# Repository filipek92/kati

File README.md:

# kati - card access system

Kati is access system developed for [club Buben](http://www.buk.cvut.cz) of [CTU Student Union](http://su.cvut.cz).

Authentication and authorization is performed by these steps:

1. user attaches identification card to reader located near the door
2. reader parses identification of the card
3. authorization request is send to IS to perform authorization and authentication
3. access to the door is granted or denied according to reply from IS server

[RaspberryPi](https://www.raspberrypi.org/) is used as remote controller located near the door.

## Deployment

Assuming you have working SSH key-based login to hosts:

```sh
cd deploy
vim hosts # edit according to your needs
ansible-playbook deploy.yml
```

## Testing

SSH to a testing Raspberry and run:

```sh
cd ~/kati
python3 start.py
```

You can also try only specific components:

```sh
python3 -m kati.reader
python3 -m kati.lock
```

Or run tests (which are heavily WIP):

```sh
python3 -m nose
```

## Developers

- [Pavel Trutman](https://github.com/PavelTrutman)
- [Tomáš Bedřich](https://github.com/tomasbedrich)
- [Tomáš Kukrál](https://github.com/tomkukral)

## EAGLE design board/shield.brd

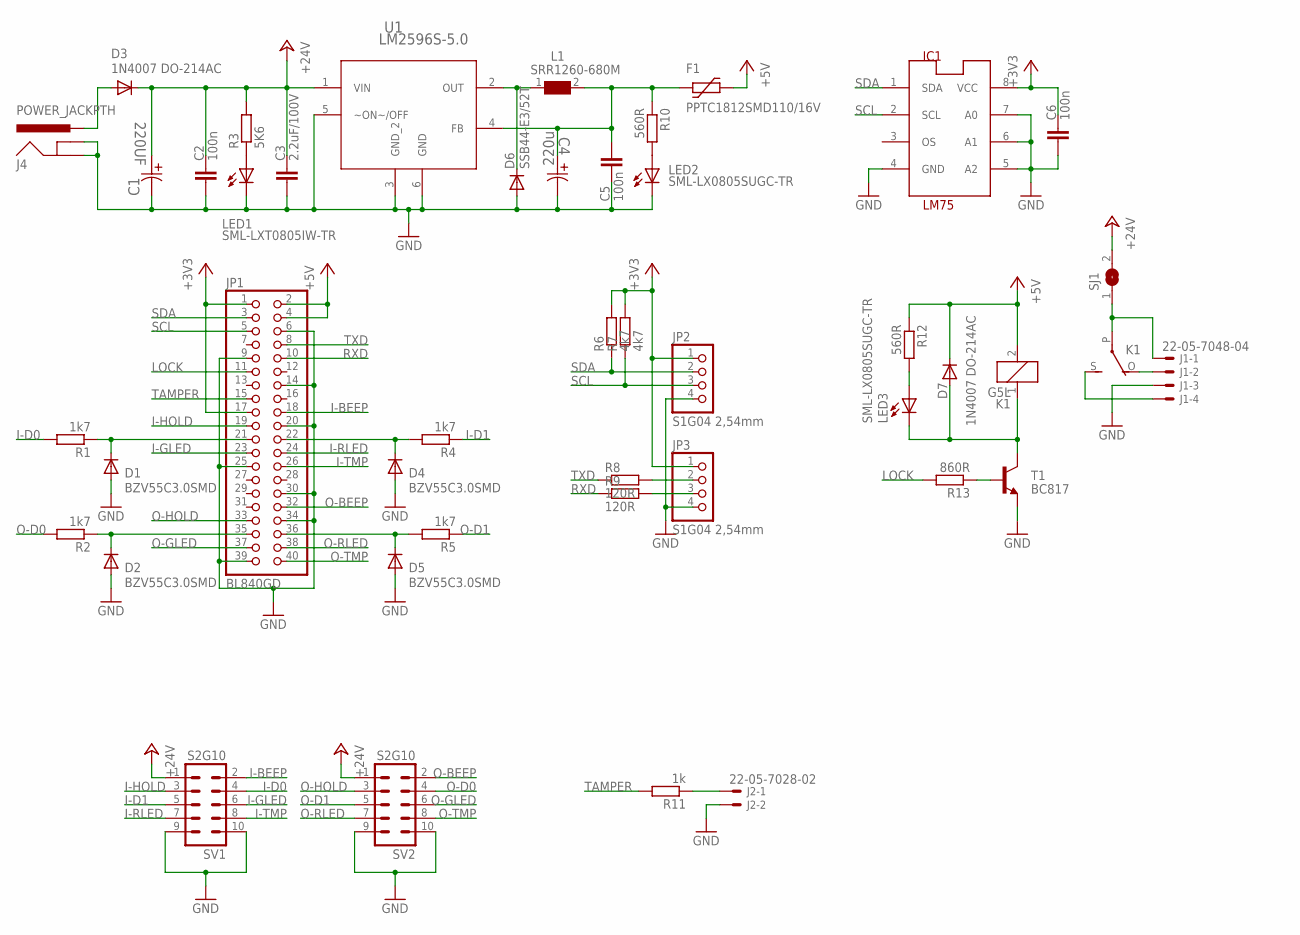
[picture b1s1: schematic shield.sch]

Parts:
C1: 220UF; CAPAE830X1050N
C2, C5, C6: 100n; C0805
C3: 2.2uF/100V; C1206
C4: 220u; CAPAE830X1050N
D1, D2, D4, D5: BZV55C3.0SMD; MINIMELF
D3, D7: 1N4007 DO-214AC; DO-214AC
D6: SSB44-E3/52T; DO214AA
F1: PPTC1812SMD110/16V; 1812L
IC1: LM75; SO8_LM75
J1: 22-05-7048-04; 7395-04
J2: 22-05-7028-02; 7395-02
J4: POWER_JACKPTH; POWER_JACK_PTH
JP1: BL840GD; 2X20
JP2, JP3: S1G04 2,54mm; 1X04
K1: G5L; G5LE
L1: SRR1260-680M; WE-PD_1260/1245/1280/1210
LED1: SML-LXT0805IW-TR; CHIPLED_0805
LED2, LED3: SML-LX0805SUGC-TR; CHIPLED_0805
R1, R2, R4, R5: 1k7; R0805
R3: 5K6; R0805
R6, R7: 4k7; R0805
R8, R9: 120R; R0805
R10, R12: 560R; R0805
R11: 1k; R0805
R13: 860R; R0805
SJ1: SJ
SV1, SV2: S2G10; MA05-2
T1: BC817; SOT23-BEC
U1: LM2596S-5.0; TO170P1435X465-6N

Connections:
+3V3: C6.2, IC1.8 (VCC), JP1.1, JP1.17, JP2.1, JP3.1, R6.2, R7.2
+5V: D7.C, F1.P$2 (2), JP1.2, JP1.4, K1.2, R12.1
+24V: C1.1, C2.2, C3.1, D3.C, R3.2, SJ1.2, SV1.1, SV2.1, U1.1 (VIN)
C: J1.1, K1.P, SJ1.1
GND: C1.2, C2.1, C3.2, C4.2, C5.1, C6.1, D1.A, D2.A, D4.A, D5.A, D6.A, IC1.4 (GND), IC1.5 (A2), IC1.6 (A1), IC1.7 (A0), J1.3, J2.2, J4.GND, J4.GNDBREAK, JP1.6, JP1.9, JP1.14, JP1.20, JP1.25, JP1.30, JP1.34, JP1.39, JP2.4, JP3.4, LED1.C, LED2.C, SV1.9, SV1.10, SV2.9, SV2.10, T1.E, U1.3 (GND_2), U1.5 (~ON~/OFF), U1.6 (GND)
I-BEEP: JP1.18, SV1.2
I-D0: R1.2, SV1.4
I-D0-3V3: D1.C, JP1.21, R1.1
I-D1: R4.1, SV1.5
I-D1-3V3: D4.C, JP1.22, R4.2
I-GLED: JP1.23, SV1.6
I-HOLD: JP1.19, SV1.3
I-RLED: JP1.24, SV1.7
I-TMP: JP1.26, SV1.8
LED: LED3.A, R12.2
LOCK: JP1.11, R13.2
LOCK_T1_R: R13.1, T1.B
unnamed: C4.1, C5.2, F1.P$1 (1), L1.2, R10.1, U1.4 (FB)
unnamed: J2.1, R11.1
unnamed: JP3.2, R8.2
unnamed: LED2.A, R10.2
unnamed: JP3.3, R9.2
unnamed: LED1.A, R3.1
unnamed: D6.C, L1.1, U1.2 (OUT)
NC: J1.2, K1.O
NO: J1.4, K1.S
O-BEEP: JP1.32, SV2.2
O-D0: R2.2, SV2.4
O-D0-3V3: D2.C, JP1.35, R2.1
O-D1: R5.1, SV2.5
O-D1-3V3: D5.C, JP1.36, R5.2
O-GLED: JP1.37, SV2.6
O-HOLD: JP1.33, SV2.3
O-RLED: JP1.38, SV2.7
O-TMP: JP1.40, SV2.8
RELAY_SW: D7.A, K1.1, LED3.C, T1.C
RXD: JP1.10, R9.1
SCL: IC1.2 (SCL), JP1.5, JP2.3, R7.1
SDA: IC1.1 (SDA), JP1.3, JP2.2, R6.1
TAMPER: JP1.15, R11.2
TXD: JP1.8, R8.1
UIN: D3.A, J4.PWR

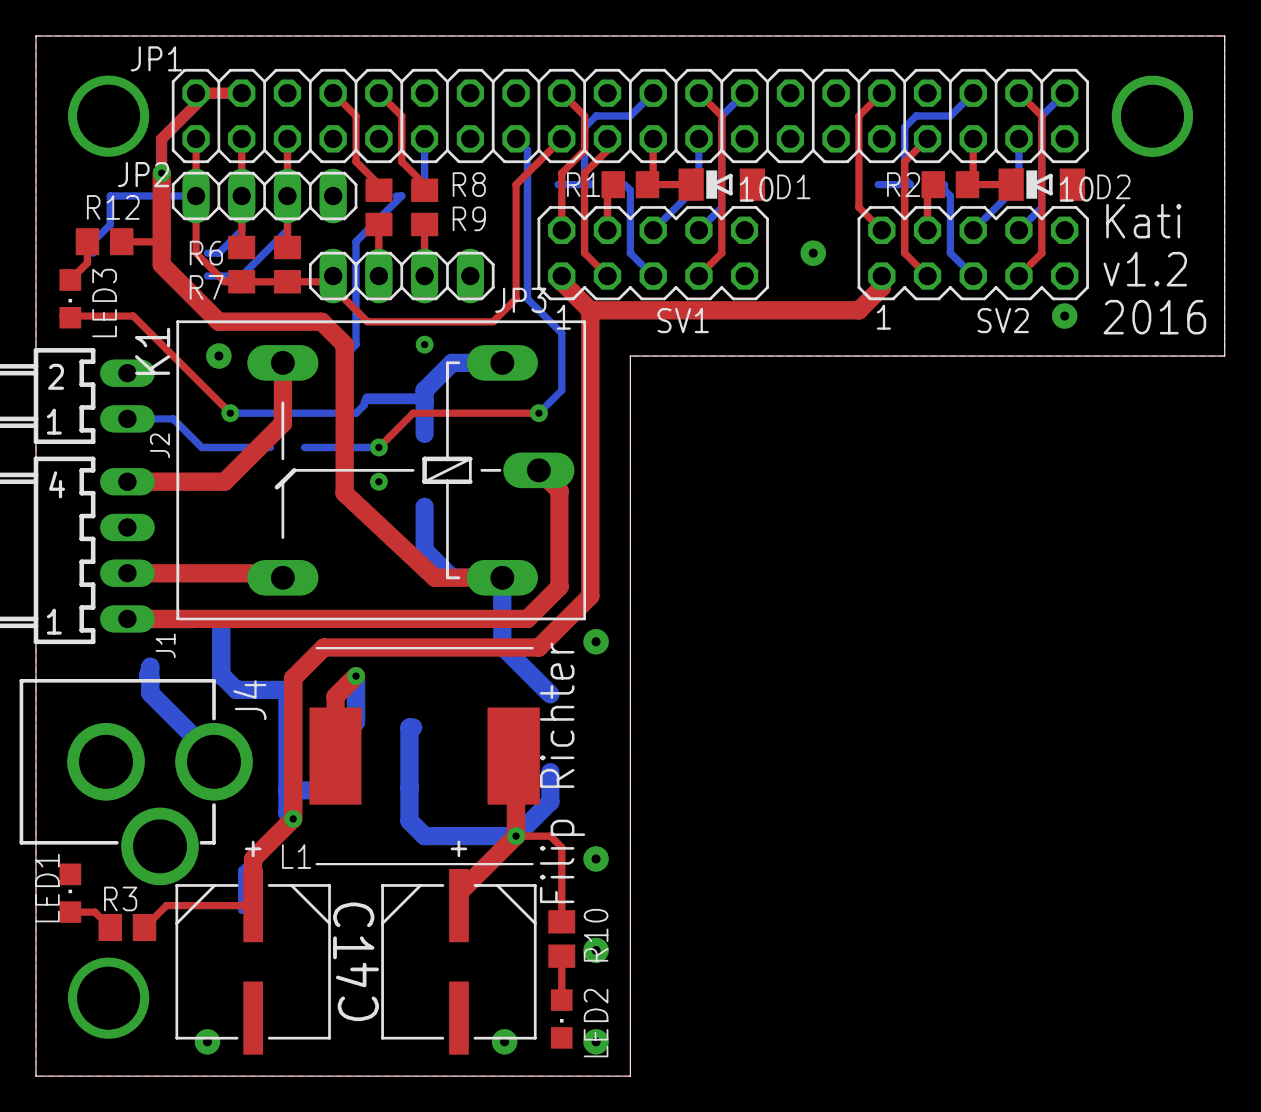
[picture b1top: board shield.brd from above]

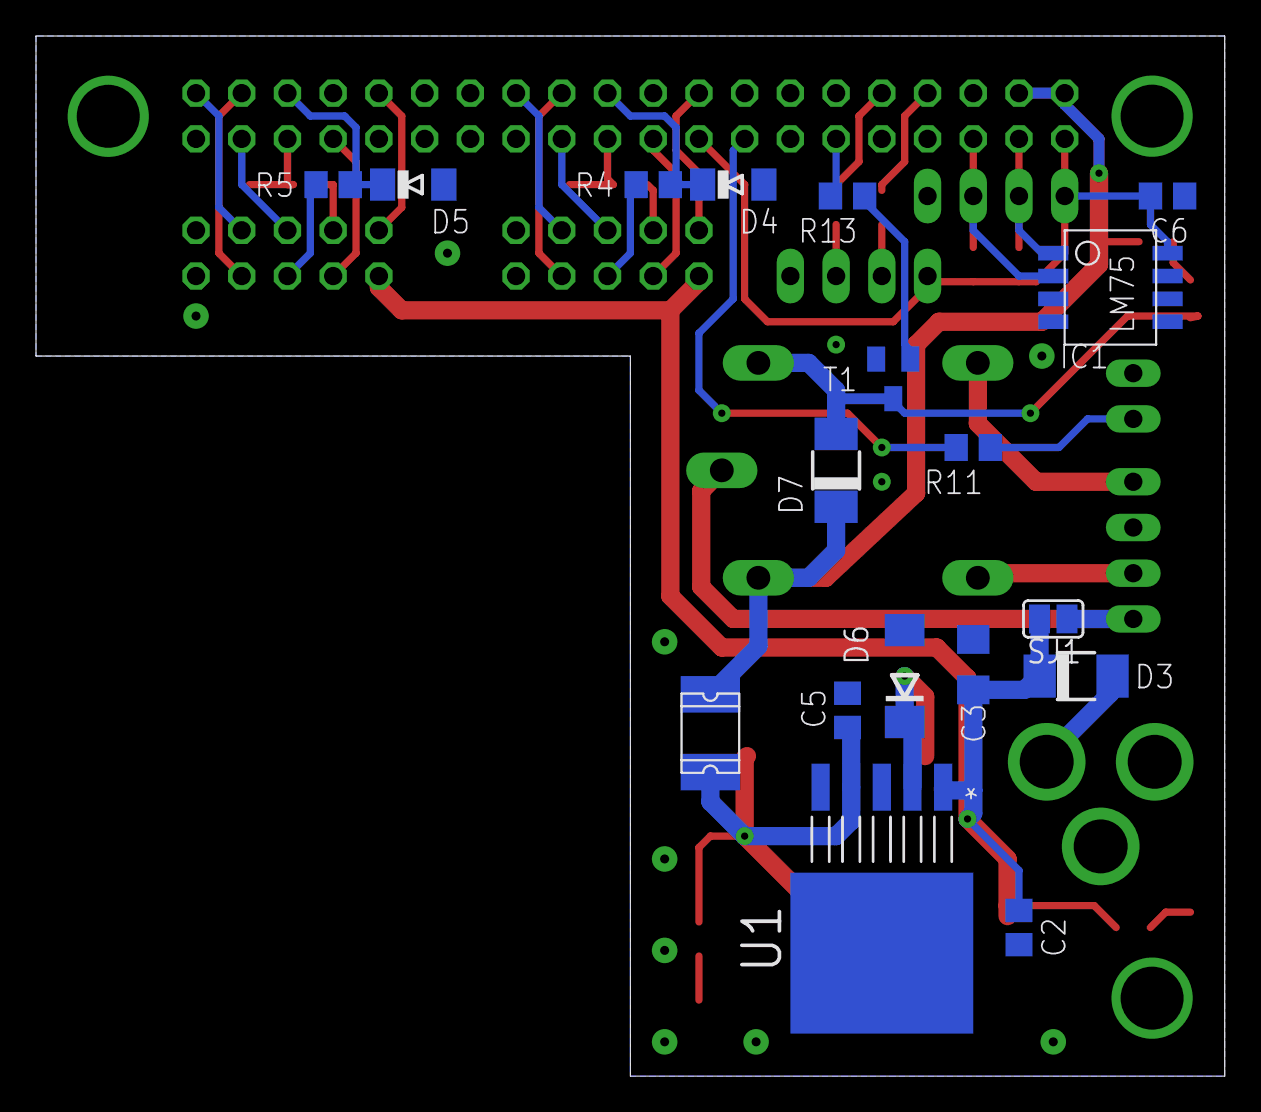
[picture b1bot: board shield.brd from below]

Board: 2 copper layers, 66.0 x 57.8 mm, 44 parts (18 on the bottom side), 42 nets.

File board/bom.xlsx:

Supplier | Part-ID | Qty | Value | Device | Package | Parts | Description | MF | MPN |  | OC_NEWARK | PACKAGE | SUPPLIER | TOLERANCE | VALUE | VOLTAGERATING | aktualni pocet | Kolik je potreba: | pozn:
GME | 832-009 | 1 | BL840GD | PINHD-2X20 | 2X20 | JP1 | PIN HEADER |  |  |  |  |  |  |  |  |  | 1 | 6 | Mame: 1 shield
GME | 906-096 | 3 | 100n | C-EUC0805 | C0805 | C2, C5, C6 | CAPACITOR, European symbol |  |  |  |  |  |  |  |  |  | 18 | 3 | Chceme: +5
GME | 901-189 | 2 | 150R | R-EU_R0805 | R0805 | R8, R9 | RESISTOR, European symbol |  |  |  |  |  |  |  |  |  | 6 | 8 | Celkem 6
GME | 917-016 | 2 | 1N4007 | DIODE-DO-214AC | DO-214AC | D3, D7 | DIODE |  |  |  |  |  |  |  |  |  | 7 | 7 | + jeden rezerva
GME | 901-178 | 1 | 1k | R-EU_R0805 | R0805 | R11 | RESISTOR, European symbol |  |  |  |  |  |  |  |  |  | 6 | 1 | Celkem 7 sad
GME | 901-594 | 4 | 1k7 | R-EU_R0805 | R0805 | R1, R2, R4, R5 | RESISTOR, European symbol |  |  |  |  |  |  |  |  |  | 14 | 14
Farnell | 1759177 | 1 | 2.2uF/100V | C-EUC1206 | C1206 | C3 | CAPACITOR, European symbol |  |  |  |  |  |  |  |  |  | 6 | 1
GME | 800-168 | 1 | 22-05-7028-02 | 22-05-7028-02 | 7395-02 | J2 | CONNECTOR |  |  |  | unknown |  |  |  |  |  | 0 | 7
GME | 800-164 | 1 | 22-05-7038-03 | 22-05-7038-03 | 7395-03 | J3 | CONNECTOR |  |  |  | unknown |  |  |  |  |  | 9 | 0
Farnell | 1539514 | 2 | 220u | EEE-FP1V221AP-CASE-F | CAPAE830X1050N | C1 | Aluminum Electrolytic Capacitors,Surface Mount Type |  | EEE-FP1V221AP |  | 94M7043 | CASE-F | PANASONIC | ±20 % | 220UF | 35V | 4 | 10
GME | 901-188 | 2 | 4k7 | R-EU_R0805 | R0805 | R6, R7 | RESISTOR, European symbol |  |  |  |  |  |  |  |  |  | 7 | 7
GME | 901-631 | 2 | 560R | R-EU_R0805 | R0805 | R10, R12 | RESISTOR, European symbol |  |  |  |  |  |  |  |  |  | 7 | 7
GME | 901-394 | 1 | 5K6 | R-EU_R0805 | R0805 | R3 | RESISTOR, European symbol |  |  |  |  |  |  |  |  |  | 6 | 1
GME | 901-368 | 1 | 860R | R-EU_R0805 | R0805 | R13 | RESISTOR, European symbol |  |  |  |  |  |  |  |  |  | 6 | 1
GME | 912-032 | 1 | BC817 | BC817-40 | SOT23-BEC | T1 | NPN Transistror |  |  |  |  |  |  |  |  |  | 6 | 1
GME | 919-008 | 4 | BZV55C3.0SMD | DIODE-MINIMELF | MINIMELF | D1, D2, D4, D5 | DIODE |  |  |  |  |  |  |  |  |  | 14 | 14
GME | 634-246 | 1 | G5L | RAS0515 | G5LE | K1 | RELAY |  |  |  | unknown |  |  |  |  |  | 0 | 7
Farnell | 1469195 | 1 | LM2596S-5.0 | LM2596S-5.0 | TO170P1435X465-6N | U1 | Step-Down Voltage Regulator |  | LM2596S-50 |  | 41K3844 | TO-263-5 | National |  |  |  | 2 | 5
GME | 969-012 | 1 | LM75 | LM75_ICN | SO8_LM75 | IC1 | Temperatursensor |  |  |  |  |  |  |  |  |  | 1 | 6
Farnell | 1597004 | 1 | PPTC1812SMD110/16V | 1812L | 1812L | F1 |  |  |  |  |  |  |  |  |  |  | 6 | 1
GME | 832-361 | 2 | S1G04 2,54mm | PINHD-1X4 | 1X04 | JP2, JP3 | PIN HEADER |  |  |  |  |  |  |  |  |  | 6 | 8
GME | 832-373 | 2 | S2G10 | MA05-2 | MA05-2 | SV1, SV2 | PIN HEADER |  |  |  | unknown |  |  |  |  |  | 2 | 12
GME | 960-023 | 2 | SML-LX0805SUGC-TR | LEDCHIPLED_0805 | CHIPLED_0805 | LED2, LED3 | LED |  |  |  |  |  |  |  |  |  | 7 | 7
GME | 960-216 | 1 | SML-LXT0805IW-TR | LEDCHIPLED_0805 | CHIPLED_0805 | I.01 | LED |  |  |  |  |  |  |  |  |  | 3 | 4
Farnell | 2212503 | 1 | SRR1260-680M | WE-PD-7447709680_1260/1245/1280/1210 | WE-PD_1260/1245/1280/1210 | L1 | SMD-Shielded Power Inductors WE-PD |  | 7447709680 |  | 08P2779 | 1210 | Wuerth Elektronik |  |  |  | 2 | 5
Farnell | 2317398 | 1 | MBRS360BT3G | DIODE-DO214AA | DO214AA | D6 | DIODE |  |  |  |  |  |  |  |  |  | 4 | 3
GME | 806-328 | 0 | WEALTHMETAL DS-214B | JACK-PLUG0 | SPC4077 | J1 | DC POWER JACK |  |  |  | unknown |  |  |  |  |  | 0 | 0
GME | 840-011 | 4 |  | KONPC-SPK-5 |  |  | Konektor |  |  |  |  |  |  |  |  |  | 3 | 25
GME | 840-004 | 20 |  | KONPC-SPK-PI |  |  | PIN rezervní |  |  |  |  |  |  |  |  |  | 0 | 140
GME | 623-373 | 3 |  | DI4M2X10 nikl VIGAN |  |  | Distanční sloupek |  |  |  |  |  |  |  |  |  | 0 | 21
GME | 623-361 | 6 |  | DA4M2X05 nikl VIGAN |  |  | Distanční sloupek |  |  |  |  |  |  |  |  |  | 0 | 42

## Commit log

2015-02-25 projekt
2015-02-25 poznámky z evernote
2015-03-10 new file: readCard.py
2015-03-10 deploy scripts
2015-05-27 Create README
    Adding basic readme and inforamtion about project.
2015-05-27 fixing README formating
2015-05-27 Pinout documentation
2015-10-07 Kati board
2015-10-08 Pour copper in TOP etch layer.
2015-10-08 Pour copper into BOTTOM etch layer.
2015-10-08 Fixed some bad diameters of holes.
2015-10-08 Artworks created
2015-10-09 Fixed minimal width of lines and spaces.
2015-10-09 Artwork Outline added.
2015-10-25 Value of resistor R1 set
2015-10-25 Images added.
2015-10-25 Technical data sent to Progoboard to mafacture the PCB.
2015-10-28 Exported wiring diagram and artworks into pdf. Added bill of material.
2016-03-20 Added Wiegand module
2016-03-20 Standard module structure, new kristin module w/ tests
2016-03-20 Added .gitignore
2016-03-20 Added pigpio installation
2016-03-21 Added reader class
2016-03-28 Fixed deploy
2016-03-28 Added GPIO numbers
2016-03-28 Changed become to per-task
2016-03-28 Changed (fixed) pins to GPIO numbers
2016-05-23 Updated output setup (HIGH = logical 0)
2016-05-23 Changed single quotes to double
2016-05-23 Added pip and requirements installation, pigpiod "creates" param
2016-05-23 Uncommented tamper handling
2016-05-23 Added main script
2016-05-24 Added lock class
2016-05-24 Wrapped readers + lock in class, more logging, added green blink
2016-05-24 Added deployment and testing to README, less logging, moved main
2016-10-01 Fixed Ansible config
2016-10-01 Updated deploy to start daemons
2016-10-01 Added Ansible *.retry and hosts files to .gitignore
2016-10-01 Refactoring, added daemon script
2016-10-01 Removed original reader script
2016-10-01 Added pidfile to deamon
2016-10-02 Updated setup to use Systemd
2016-10-04 Added error handling when access request fails
2016-10-04 Added SIGTERM and SIGINT processing
2016-10-04 Deploy timezone config, removed Ansible hosts
2016-10-04 Updated README testing instructions + header
2016-10-04 Fixed signal handler
2016-10-17 Shield version 2 created and routed
2016-10-17 Minor changes in PCB design
2016-10-17 Led added, parts renumbered
2016-10-17 Names reordered
2016-10-17 Minor silkscreen changes
2016-10-17 Factory data generated
2016-10-17 Ignore zip files
2016-10-27 Bill of material
2016-10-27 Old board replaced
2016-11-05 Used the_reader.text_id for API call
2016-11-06 Change of cloning kati repo
2016-11-06 Added connecting diagram
2016-12-08 DC Jack connector replaced
2016-12-08 Relay connector extended with common pin, connection to +24V is optional by solder bridge
2016-12-14 Fixed DRC Error, minor changes
2016-12-14 Labels position optimized
2016-12-14 Solder jumper position fix
2016-12-14 Silkscreen corrected
2016-12-14 Gerber data generated
2016-12-14 Silkscreen modification
2016-12-14 Text fixed
2016-12-23 Updated deploy timezone setting
2016-12-23 Deploy adds Kristin IP to hosts
2016-12-23 Added LRU cache for access checks
2016-12-23 Changed deploy repo URL
2016-12-23 Updated repo URL for systemd service too
2017-01-04 Add aktualni stavy soucastek a kolik je potreba dokoupit do bom.xlsx
2017-01-19 Connecting updated
2017-02-07 Objednávka Filip Richter Leden 2017
2017-02-07 Dodávka 07.02.2017, Filip Richter
2017-02-07 Update of connecting diagram, export to image

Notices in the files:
parts and their libraries:
SparkFun-Connectors: Licensing: Creative Commons ShareAlike 4.0 International - https://creativecommons.org/licenses/by-sa/4.0
